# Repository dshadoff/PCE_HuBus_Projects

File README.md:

# PC Engine HuBus Project

Rather than create separate repositories for each of the projects, this repository will
hold all of my projects related to the HuBus (based off of the HuCard port on the PC Engine).

## HuCard_Breakout

This is a board - actually 2 boards - which are a total of 2.4mm thick, and plug into
the HuCard slot.  A HuCard connector (rare, unfortunately) is attached at the end, but
a 40-pin (2x20) Raspberry Pi GPIO-type header header is mounted in the middle, exposing
all signals.  This becomes the basis of the bus; various memory-based peripherals.

### How to build:
You will need both HuCard_Breakout and HuCard_Breakout_under boards - the gerber files
are included:
- Make the HuCard_Breakout board 1.6mm thick, I use ENIG finish - not as durable as hard gold, but much cheaper
- Make the HuCard_Breakout_under board 0.8mm thick
You will probably want a stencil, since the two boards areintended to be held together
with solder:  I apply a low-temperature solder paste along the metallized edge, and bake
with a regular lead solder profile, with the board held together by miniature letter clips.

There are often tiny spheres of solder at the edges, which can be removed easily with a
light scrape along the edge.

Once the board is properly attached, don't forget to sand a bevel on the leading edge of
the card-edge: I use sandpaper of about 180 grit, and sand gently by hand until a bevel of
slightly less than 1mm exists evenly.

For attaching the header (and card edge connector), I clip the leads as close as possible to
the board **before soldering**, so that no sharp edges remain after the soldering.
Ideally, the solder is level, but a gentle convex curve is acceptable.

## HuMem board

This board attaches to the bus, and presents the following to the bus:
- Flash memory (SST39SF010A, PDIP) at banks $90 through $9F
- Static RAM (LY625128SL-55LLI available as part of JLCPCB's SMD assembly service) at banks $B0-$EF

I have included the gerbers and relevant bom.csv and assembly.csv files to get these boards
assembled by JLCPCB, but you will still need the following parts:
- ATF16V8BQL, PDIP (and socket), and an EPROM programmer capable of programming these
- SST39SF010A, PDIP (and scoket), and as EPROM programmer capable of programming these
- a longer-than-usual 2x20 DIP header, such as PRT-16763 from Sparkfun

### How to build
Assembly should be straightforward - just remember that the long pins server as next-level
pin headers for the bus, and that the IC chips don't all face in the same direction.

### GAL logic
The GAL (ATF16V8BQL) serves as the address decoder on this board, and can be reprogrammed to
locate these memories anywhere in the address space.

The logic for this was assembled using an obsolete software package, WinCUPL, because there are
very few ways to program for 5V logic anymore (and I didn't want to use level-shift for everything
on this board).  The key files to reference in that folder are:
- MEMSEL.PLD - the CUPL source code; should be more or less self-explanatory
- MEMSEL.si  - simulation test inputs/outputs for validation of the design
- MEMSEL.jed - used for programming the GAL device

## HuUSB board

This board attaches to the bus, and presents an FTDI FT245RL to the bus:
- at $FF:$1C00 : data input/output
- at $FF:$1C01 : status
  - bits 7-4 (most-significant nybble):  value $Ax for identification
  - bits 3-2 : value 0, 0
  - bit  1 : TX ready : when low, it is ready for data to be sent to USB
  - bit  0 : RX ready : when low, there is data waiting in the FIFO to be read

Transfer speed is faster than the PC Engine can process at hundreds of kilobytes per second

I have included the gerbers and relevant bom.csv and assembly.csv files to get these boards
assembled by JLCPCB, but you will still need the following parts:
- ATF22V10CQZ, PDIP (and socket), and an EPROM programmer capable of programming these
- a longer-than-usual 2x20 DIP header, such as PRT-16763 from Sparkfun
- a USB mini cable (older style; these are more durable than the micro connectors)

### GAL logic
The GAL (ATF22V10CQZ) serves as the address decoder on this board, and can be reprogrammed to
locate the USB memory map anywhere in the address space - but it only decodes 13 bits of the address,
so it reserves 256 bytes for the sake of only 2.

The logic for this was assembled using an obsolete software package, WinCUPL, because there are
very few ways to program for 5V logic anymore (and I didn't want to use level-shift for everything
on this board).  The key files to reference in that folder are:
- USBSEL.PLD - the CUPL source code; should be more or less self-explanatory
- USBSEL.jed - used for programming the GAL device

## HuXtension board

This is something I've wanted for perhaps 30 years.
Perhaps you've seen the GPIO extenders for Raspberry Pi, which have a ribbon cable and a small board,
taking all GPIOs and placing them into a breadboard neatly.  Those boards have many pins connected
to ground which would be VERY BAD for this system.

But the ribbon cables are still good, and the board itself is basically trivial.

All you will need are pin headers to go into a breadboard, and a 2x20 GPIO pin header to put the
ribbon cable on.

## All Boards, Stacked:

## Notes:

I designed all boards using the free version of EAGLE (2-layer, less than 100mm
on both X- and Y-axes).  The gerbers are included in this repository, in case you
want to get your own set made.

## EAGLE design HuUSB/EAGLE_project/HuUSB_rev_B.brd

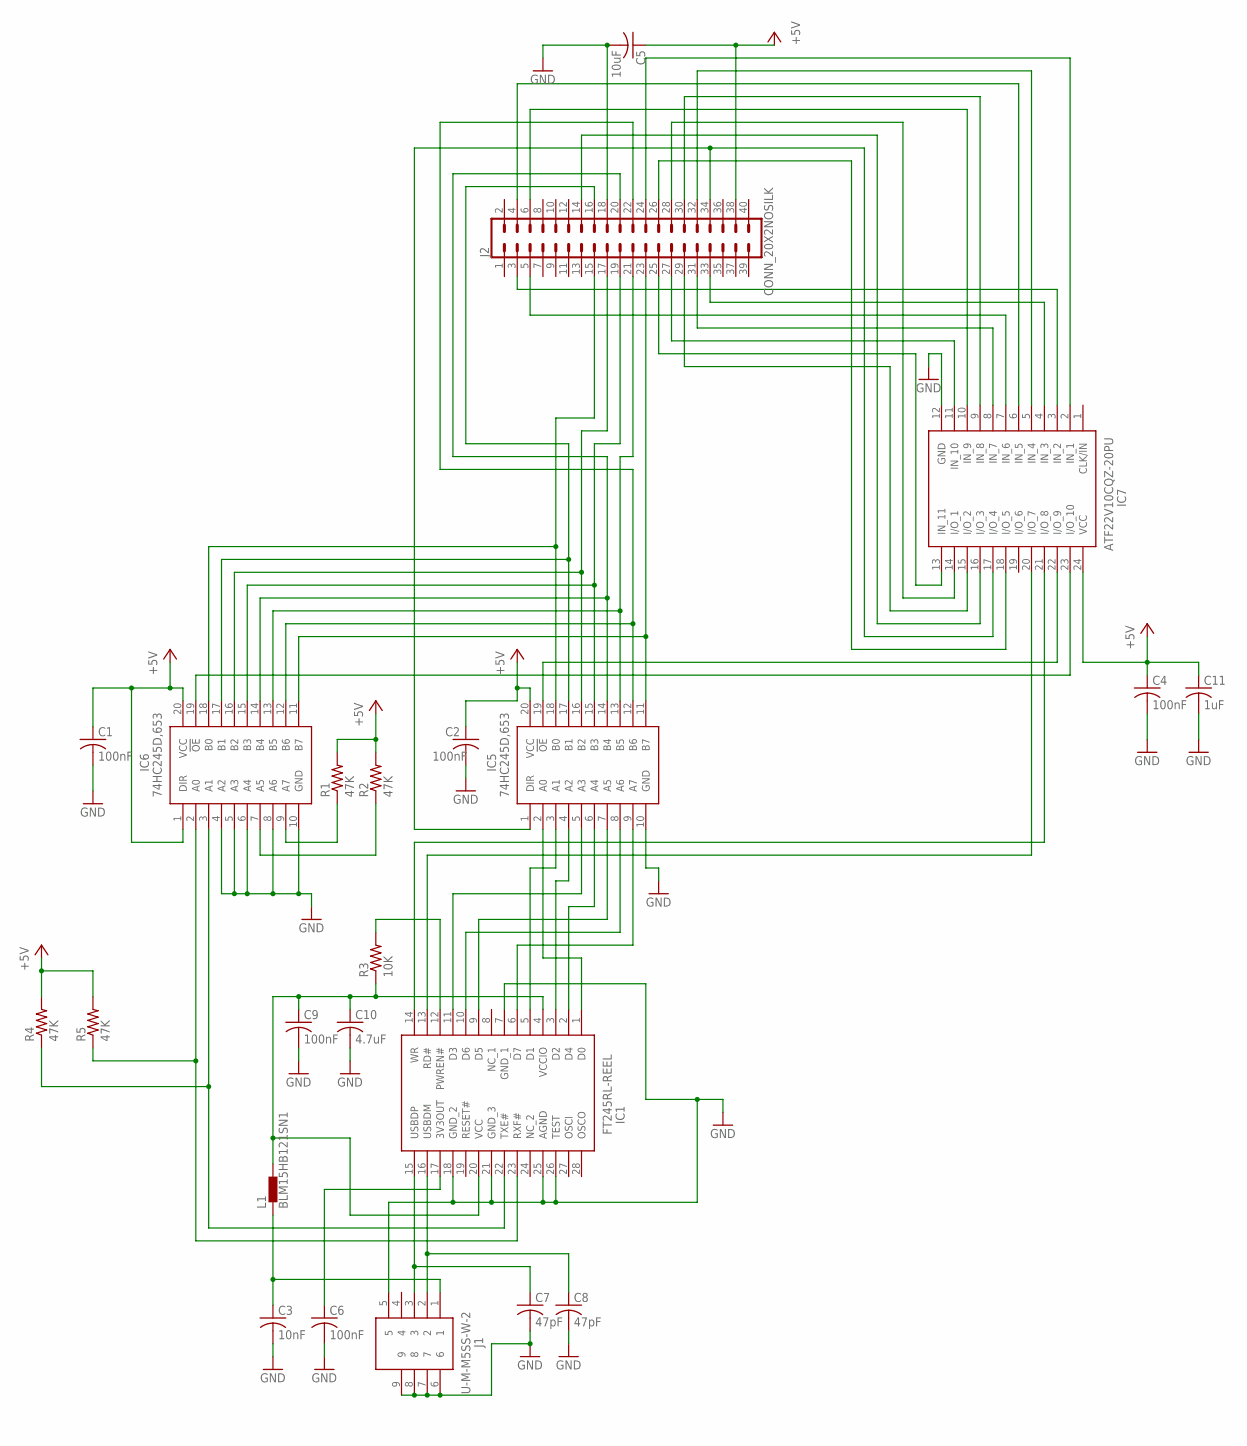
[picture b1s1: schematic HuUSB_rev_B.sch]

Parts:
C1, C2, C4, C6, C9: 100nF; C0603
C3: 10nF; C0603
C5: 10uF; C0805
C7, C8: 47pF; C0603
C10: 4.7uF; C0603
C11: 1uF; C0603
IC1: FT245RL-REEL; SOP65P778X200-28N
IC5, IC6: 74HC245D,653; SOIC127P1032X265-20N
IC7: ATF22V10CQZ-20PU; DIP794W56P254L3188H533Q24N
J1: U-M-M5SS-W-2
J2: CONN_20X2NOSILK; 2X20_NOSILK
L1: BLM15HB121SN1; 0402
R1, R2, R4, R5: 47K; R0603
R3: 10K; R0603

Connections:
+5V: C1.1, C2.1, C4.1, C5.1, C11.1, IC5.20 (VCC), IC6.1 (DIR), IC6.20 (VCC), IC7.24 (VCC), J2.38, R1.2, R2.2, R4.2, R5.2
GND: C1.2, C2.2, C3.2, C4.2, C5.2, C6.2, C7.2, C8.2, C9.2, C10.2, C11.2, IC1.7 (GND_1), IC1.18 (GND_2), IC1.21 (GND_3), IC1.25 (AGND), IC1.26 (TEST), IC5.10 (GND), IC6.4 (A2), IC6.5 (A3), IC6.6 (A4), IC6.8 (A6), IC6.10 (GND), IC7.12 (GND), J1.5, J1.6, J1.7, J1.8, J1.9, J2.18
unnamed: IC7.2 (IN_1), J2.24
unnamed: IC7.3 (IN_2), J2.3
unnamed: IC7.4 (IN_3), J2.33
unnamed: IC7.5 (IN_4), J2.32
unnamed: IC7.6 (IN_5), J2.4
unnamed: IC7.7 (IN_6), J2.5
unnamed: IC7.8 (IN_7), J2.31
unnamed: IC7.9 (IN_8), J2.30
unnamed: IC7.10 (IN_9), J2.6
unnamed: IC7.11 (IN_10), J2.27
unnamed: IC7.13 (IN_11), J2.25
unnamed: IC7.14 (I/O_1), J2.28
unnamed: IC7.15 (I/O_2), J2.29
unnamed: IC7.16 (I/O_3), J2.14
unnamed: IC5.1 (DIR), IC7.17 (I/O_4), J2.34
unnamed: IC7.18 (I/O_5), J2.26
unnamed: IC1.14 (WR), IC7.21 (I/O_8)
unnamed: IC1.1 (D0), IC5.2 (A0)
unnamed: IC6.9 (A7), R1.1
unnamed: IC1.2 (D4), IC5.6 (A4)
unnamed: IC1.11 (D3), IC5.5 (A3)
unnamed: IC1.5 (D1), IC5.3 (A1)
unnamed: IC1.9 (D5), IC5.7 (A5)
unnamed: IC1.10 (D6), IC5.8 (A6)
unnamed: IC1.6 (D7), IC5.9 (A7)
unnamed: IC6.19 (!OE), IC7.23 (I/O_10)
unnamed: IC5.19 (!OE), IC7.22 (I/O_9)
unnamed: IC5.18 (B0), IC6.18 (B0), J2.15
unnamed: IC1.13 (RD#), IC7.20 (I/O_7)
unnamed: IC5.17 (B1), IC6.17 (B1), J2.16
unnamed: IC5.16 (B2), IC6.16 (B2), J2.17
unnamed: IC5.15 (B3), IC6.15 (B3), J2.19
unnamed: IC5.14 (B4), IC6.14 (B4), J2.20
unnamed: IC5.13 (B5), IC6.13 (B5), J2.21
unnamed: IC5.12 (B6), IC6.12 (B6), J2.22
unnamed: IC5.11 (B7), IC6.11 (B7), J2.23
unnamed: IC1.3 (D2), IC5.4 (A2)
unnamed: C6.1, IC1.17 (3V3OUT)
unnamed: IC6.7 (A5), R2.1
unnamed: C7.1, IC1.15 (USBDP), J1.3
unnamed: C8.1, IC1.16 (USBDM), J1.2
unnamed: C9.1, C10.1, IC1.4 (VCCIO), IC1.20 (VCC), L1.2, R3.1
unnamed: IC1.12 (PWREN#), R3.2
unnamed: C3.1, J1.1, L1.1
unnamed: IC1.22 (TXE#), IC6.3 (A1), R4.1
unnamed: IC1.23 (RXF#), IC6.2 (A0), R5.1

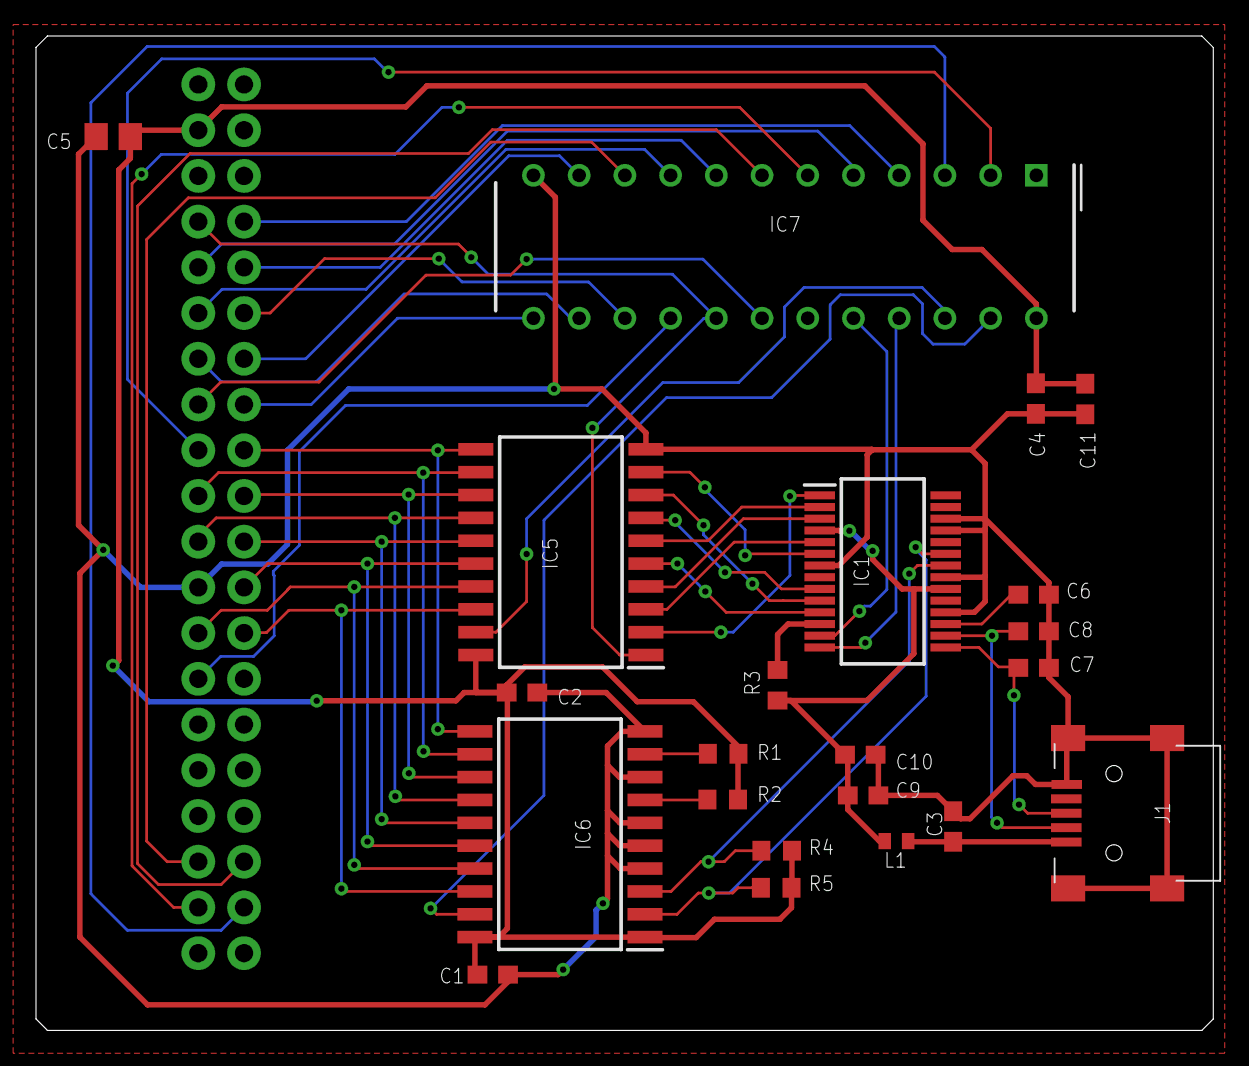
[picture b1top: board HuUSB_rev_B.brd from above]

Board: 2 copper layers, 65.4 x 55.2 mm, 23 parts (0 on the bottom side), 48 nets.

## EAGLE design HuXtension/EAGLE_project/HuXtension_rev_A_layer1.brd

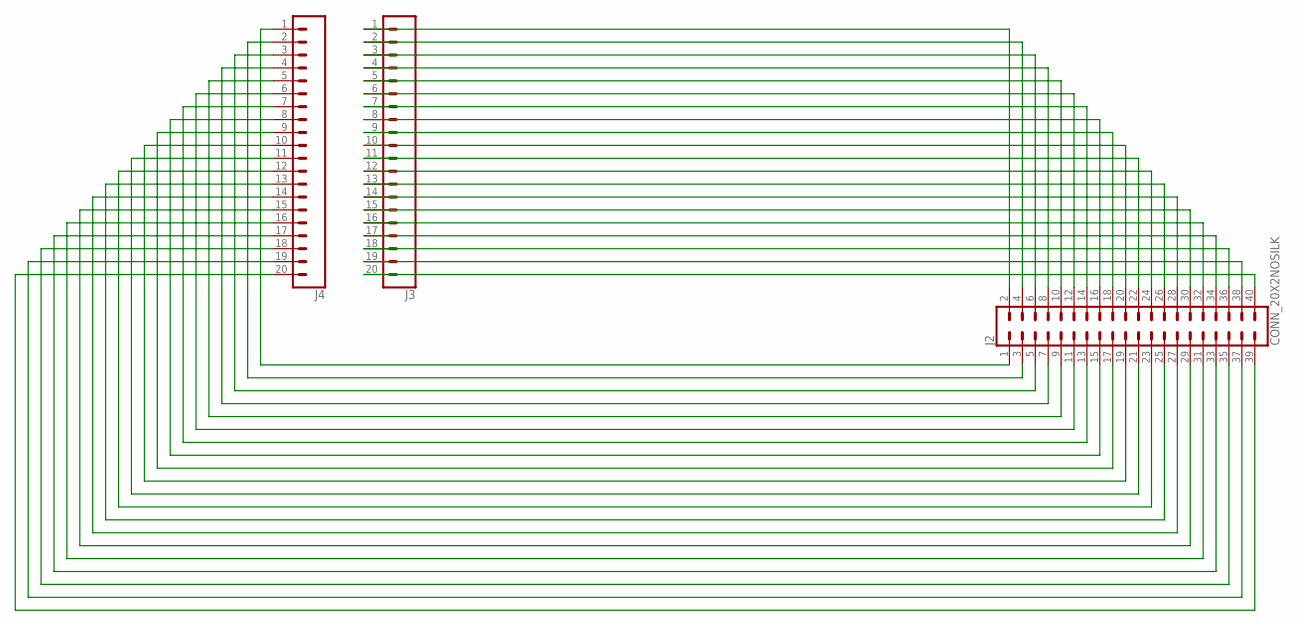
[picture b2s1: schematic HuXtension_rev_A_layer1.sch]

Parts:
J2: CONN_20X2NOSILK; 2X20_NOSILK
J3, J4: CONN_20NOSILK; 1X20_NOSILK

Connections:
unnamed: J2.1, J4.1
unnamed: J2.3, J4.2
unnamed: J2.5, J4.3
unnamed: J2.7, J4.4
unnamed: J2.9, J4.5
unnamed: J2.11, J4.6
unnamed: J2.15, J4.8
unnamed: J2.17, J4.9
unnamed: J2.19, J4.10
unnamed: J2.21, J4.11
unnamed: J2.23, J4.12
unnamed: J2.25, J4.13
unnamed: J2.27, J4.14
unnamed: J2.2, J3.1
unnamed: J2.29, J4.15
unnamed: J2.4, J3.2
unnamed: J2.31, J4.16
unnamed: J2.6, J3.3
unnamed: J2.33, J4.17
unnamed: J2.8, J3.4
unnamed: J2.35, J4.18
unnamed: J2.10, J3.5
unnamed: J2.37, J4.19
unnamed: J2.39, J4.20
unnamed: J2.40, J3.20
unnamed: J2.13, J4.7
unnamed: J2.38, J3.19
unnamed: J2.36, J3.18
unnamed: J2.34, J3.17
unnamed: J2.32, J3.16
unnamed: J2.12, J3.6
unnamed: J2.14, J3.7
unnamed: J2.16, J3.8
unnamed: J2.18, J3.9
unnamed: J2.20, J3.10
unnamed: J2.22, J3.11
unnamed: J2.24, J3.12
unnamed: J2.26, J3.13
unnamed: J2.28, J3.14
unnamed: J2.30, J3.15

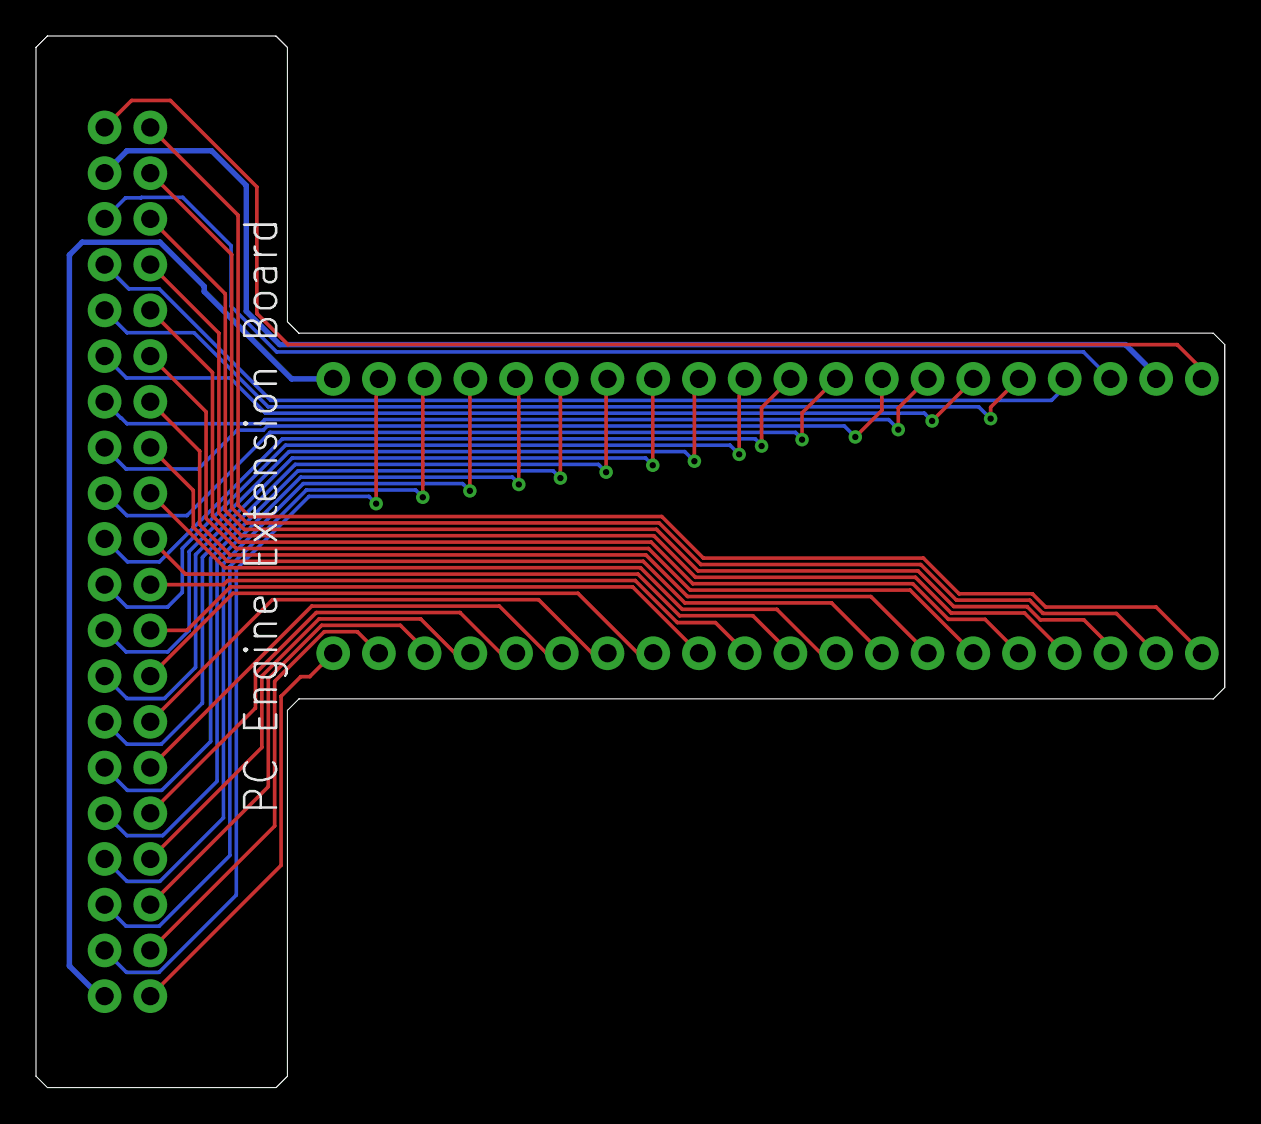
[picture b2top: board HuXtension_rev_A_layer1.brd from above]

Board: 2 copper layers, 66.0 x 58.4 mm, 3 parts (0 on the bottom side), 40 nets.

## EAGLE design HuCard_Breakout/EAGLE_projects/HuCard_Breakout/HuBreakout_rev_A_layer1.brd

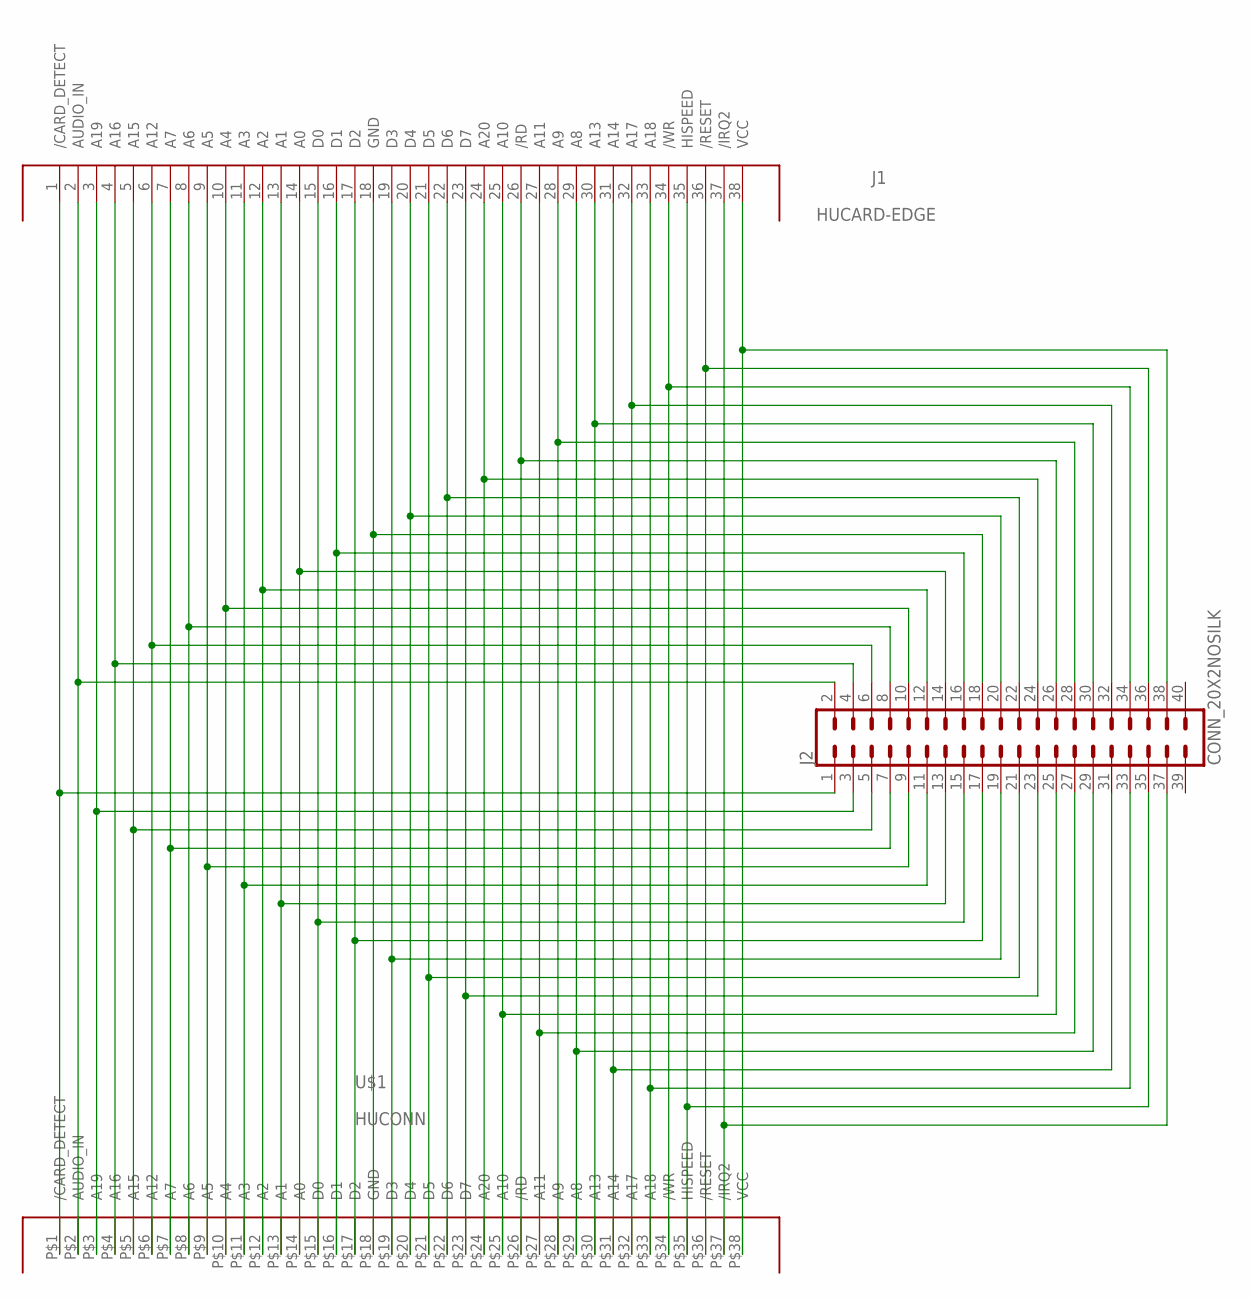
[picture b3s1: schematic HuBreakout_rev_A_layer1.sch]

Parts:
J1: HUCARD-EDGE
J2: CONN_20X2NOSILK; 2X20_NOSILK
U$1: HUCONN

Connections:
GND: J1.18 (GND), J2.18, U$1.P$18 (GND)
unnamed: J1.1 (/CARD_DETECT), J2.1, U$1.P$1 (/CARD_DETECT)
unnamed: J1.2 (AUDIO_IN), J2.2, U$1.P$2 (AUDIO_IN)
unnamed: J1.3 (A19), J2.3, U$1.P$3 (A19)
unnamed: J1.4 (A16), J2.4, U$1.P$4 (A16)
unnamed: J1.5 (A15), J2.5, U$1.P$5 (A15)
unnamed: J1.6 (A12), J2.6, U$1.P$6 (A12)
unnamed: J1.7 (A7), J2.7, U$1.P$7 (A7)
unnamed: J1.8 (A6), J2.8, U$1.P$8 (A6)
unnamed: J1.9 (A5), J2.9, U$1.P$9 (A5)
unnamed: J1.10 (A4), J2.10, U$1.P$10 (A4)
unnamed: J1.11 (A3), J2.11, U$1.P$11 (A3)
unnamed: J1.12 (A2), J2.12, U$1.P$12 (A2)
unnamed: J1.14 (A0), J2.14, U$1.P$14 (A0)
unnamed: J1.15 (D0), J2.15, U$1.P$15 (D0)
unnamed: J1.16 (D1), J2.16, U$1.P$16 (D1)
unnamed: J1.17 (D2), J2.17, U$1.P$17 (D2)
unnamed: J1.19 (D3), J2.19, U$1.P$19 (D3)
unnamed: J1.20 (D4), J2.20, U$1.P$20 (D4)
unnamed: J1.21 (D5), J2.21, U$1.P$21 (D5)
unnamed: J1.22 (D6), J2.22, U$1.P$22 (D6)
unnamed: J1.23 (D7), J2.23, U$1.P$23 (D7)
unnamed: J1.24 (A20), J2.24, U$1.P$24 (A20)
unnamed: J1.25 (A10), J2.25, U$1.P$25 (A10)
unnamed: J1.26 (/RD), J2.26, U$1.P$26 (/RD)
unnamed: J1.27 (A11), J2.27, U$1.P$27 (A11)
unnamed: J1.28 (A9), J2.28, U$1.P$28 (A9)
unnamed: J1.29 (A8), J2.29, U$1.P$29 (A8)
unnamed: J1.30 (A13), J2.30, U$1.P$30 (A13)
unnamed: J1.31 (A14), J2.31, U$1.P$31 (A14)
unnamed: J1.32 (A17), J2.32, U$1.P$32 (A17)
unnamed: J1.33 (A18), J2.33, U$1.P$33 (A18)
unnamed: J1.34 (/WR), J2.34, U$1.P$34 (/WR)
unnamed: J1.35 (HISPEED), J2.35, U$1.P$35 (HISPEED)
unnamed: J1.36 (/RESET), J2.36, U$1.P$36 (/RESET)
unnamed: J1.37 (/IRQ2), J2.37, U$1.P$37 (/IRQ2)
unnamed: J1.13 (A1), J2.13, U$1.P$13 (A1)
VCC: J1.38 (VCC), J2.38, U$1.P$38 (VCC)

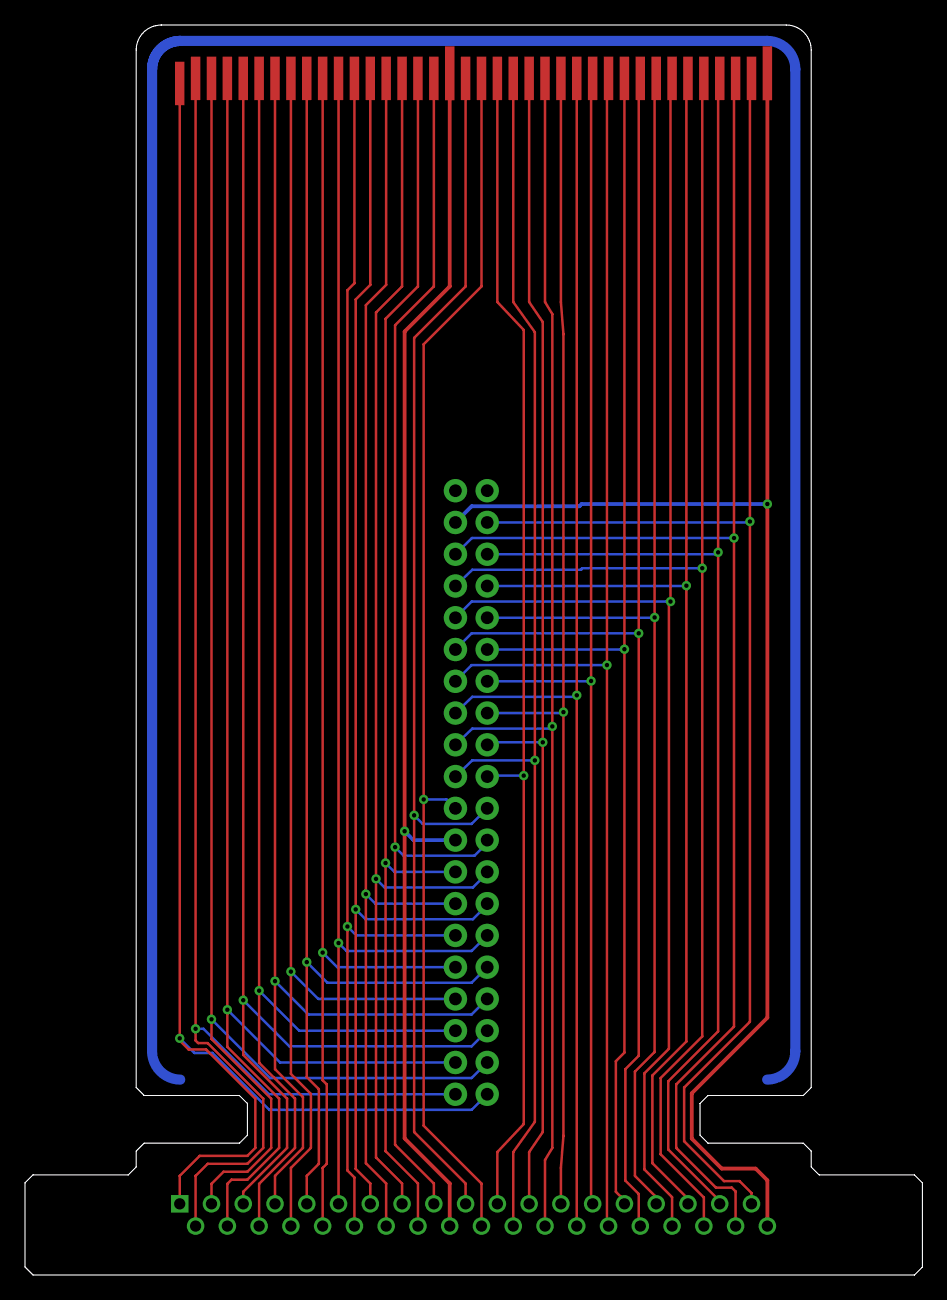
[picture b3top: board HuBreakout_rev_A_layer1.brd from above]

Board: 2 copper layers, 71.8 x 99.9 mm, 3 parts (0 on the bottom side), 38 nets.

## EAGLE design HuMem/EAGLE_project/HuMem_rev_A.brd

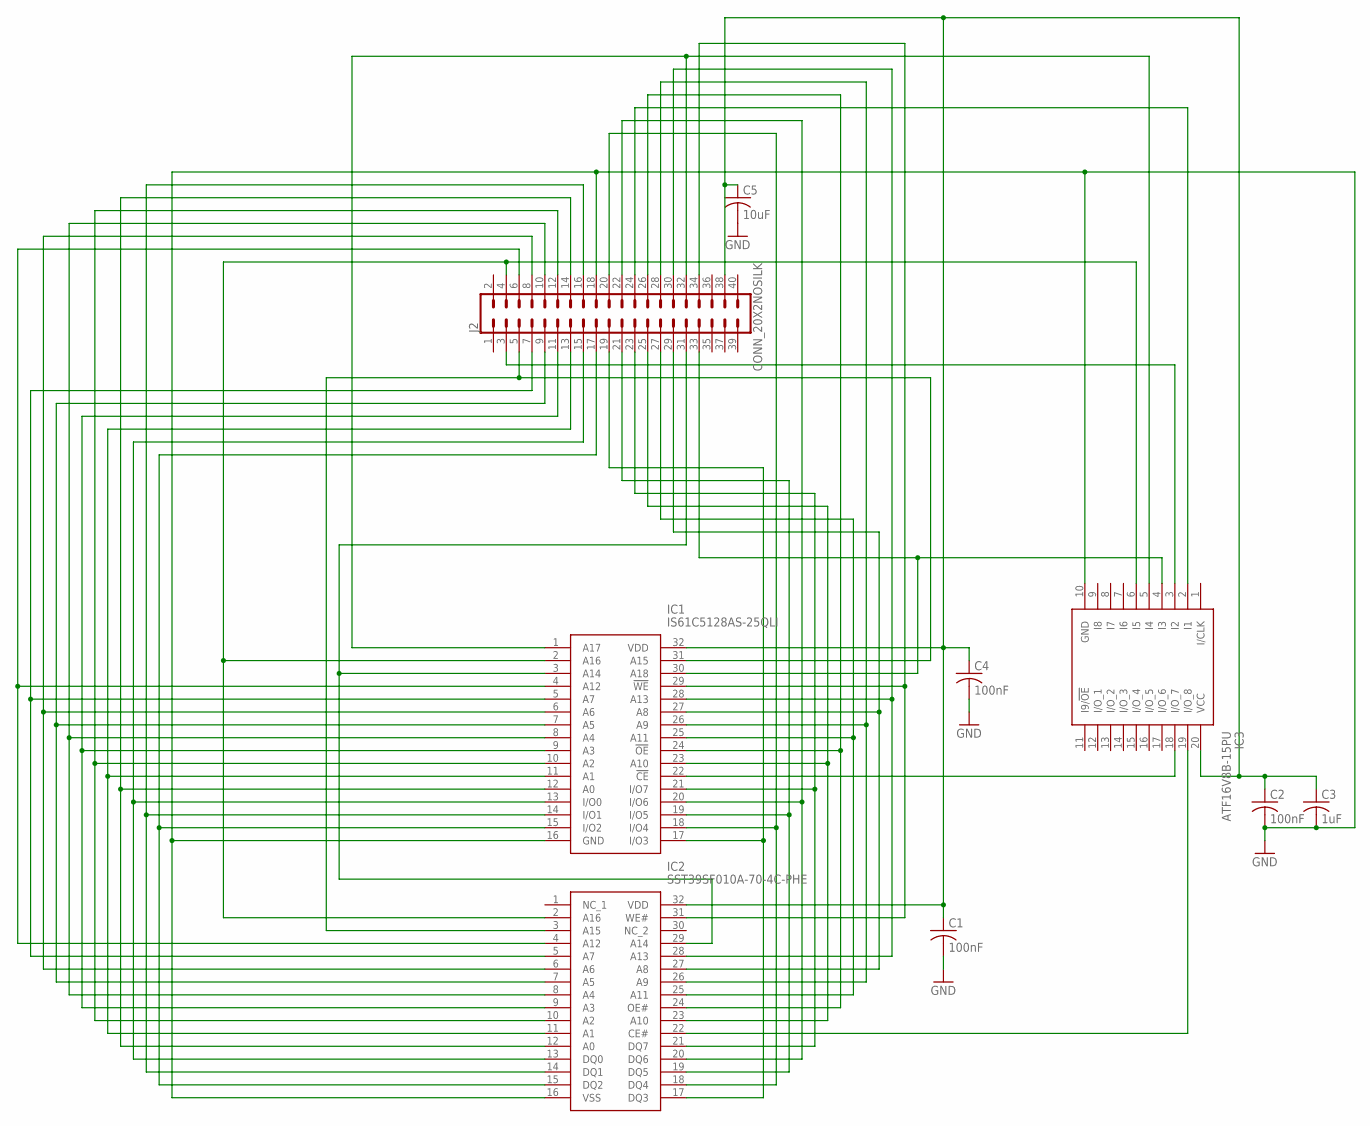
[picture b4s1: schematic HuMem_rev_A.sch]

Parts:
C1, C2, C4: 100nF; C0603
C3: 1uF; C0603
C5: 10uF; C0805
IC1: IS61C5128AS-25QLI; SOIC127P1412X305-32N
IC2: SST39SF010A-70-4C-PHE; DIP1556W56P254L4191H508Q32N
IC3: ATF16V8B-15PU; DIP794W59P254L2591H533Q20N
J2: CONN_20X2NOSILK; 2X20_NOSILK

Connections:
A0: IC1.12 (A0), IC2.12 (A0), J2.14
A1: IC1.11 (A1), IC2.11 (A1), J2.13
A2: IC1.10 (A2), IC2.10 (A2), J2.12
A3: IC1.9 (A3), IC2.9 (A3), J2.11
A4: IC1.8 (A4), IC2.8 (A4), J2.10
A5: IC1.7 (A5), IC2.7 (A5), J2.9
A6: IC1.6 (A6), IC2.6 (A6), J2.8
A7: IC1.5 (A7), IC2.5 (A7), J2.7
A8: IC1.27 (A8), IC2.27 (A8), J2.29
A9: IC1.26 (A9), IC2.26 (A9), J2.28
A10: IC1.23 (A10), IC2.23 (A10), J2.25
A11: IC1.25 (A11), IC2.25 (A11), J2.27
A12: IC1.4 (A12), IC2.4 (A12), J2.6
A13: IC1.28 (A13), IC2.28 (A13), J2.30
A14: IC1.3 (A14), IC2.29 (A14), J2.31
A15: IC1.31 (A15), IC2.3 (A15), J2.5
A16: IC1.2 (A16), IC2.2 (A16), IC3.6 (I5), J2.4
A17: IC1.1 (A17), IC3.5 (I4), J2.32
A18: IC1.30 (A18), IC3.4 (I3), J2.33
A19: IC3.3 (I2), J2.3
A20: IC3.2 (I1), J2.24
D0: IC1.13 (I/O0), IC2.13 (DQ0), J2.15
D1: IC1.14 (I/O1), IC2.14 (DQ1), J2.16
D2: IC1.15 (I/O2), IC2.15 (DQ2), J2.17
D3: IC1.17 (I/O3), IC2.17 (DQ3), J2.19
D4: IC1.18 (I/O4), IC2.18 (DQ4), J2.20
D5: IC1.19 (I/O5), IC2.19 (DQ5), J2.21
D6: IC1.20 (I/O6), IC2.20 (DQ6), J2.22
D7: IC1.21 (I/O7), IC2.21 (DQ7), J2.23
GND: C1.2, C2.2, C3.2, C4.2, C5.2, IC1.16 (GND), IC2.16 (VSS), IC3.10 (GND), J2.18
unnamed: C1.1, C2.1, C3.1, C4.1, C5.1, IC1.32 (VDD), IC2.32 (VDD), IC3.20 (VCC), J2.38
unnamed: IC2.22 (CE#), IC3.19 (I/O_8)
unnamed: IC1.22 (!CE), IC3.18 (I/O_7)
RD: IC1.24 (!OE), IC2.24 (OE#), J2.26
WR: IC1.29 (!WE), IC2.31 (WE#), J2.34

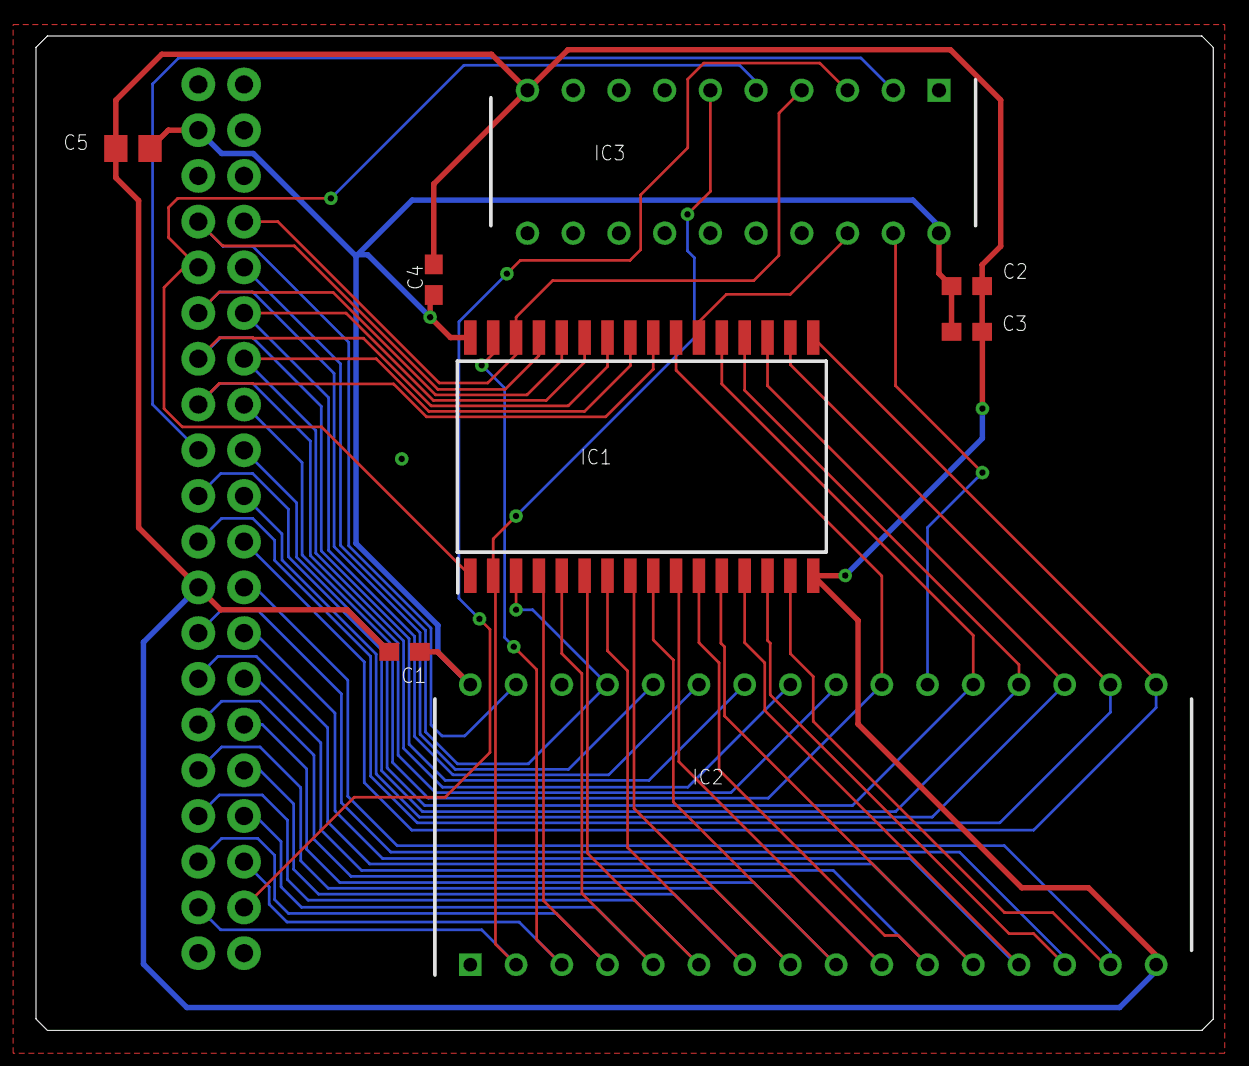
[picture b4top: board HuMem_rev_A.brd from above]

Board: 2 copper layers, 65.4 x 55.2 mm, 9 parts (0 on the bottom side), 35 nets.

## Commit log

2021-02-13 Initial Check-in
2021-02-27 Add HuUSB board
2021-02-27 Added HuXtension
2021-02-27 Add picture of all boards, stacked
2021-03-04 Add pull-up resistors to status bits coming from FT245RL

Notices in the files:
HuCard_Breakout/EAGLE_projects/HuCard_Breakout/HuBreakout_rev_A_layer1.brd:
(c) 2021
HuUSB/EAGLE_project/HuUSB_rev_B.brd:
(c) 2021, Dave Shadoff
parts and their libraries:
SparkFun-Connectors: Licensing: Creative Commons ShareAlike 4.0 International - https://creativecommons.org/licenses/by-sa/4.0
